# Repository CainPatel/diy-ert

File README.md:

# diy-ert

<!-- photo of the breadboard build / field setup goes here -->

A four electrode earth resistivity meter (Wenner array) built from scratch
in about a month, for roughly $150 in parts. Commercial instruments that
make the same measurement start above $20,000.

This repo is written as an engineering log. Four ADS1115 ADCs died during
development, all from the same root cause, and the
[failure log](docs/failure-log.md) is probably the most useful file here.
Read it before powering anything up.

The custom PCB, designed after the breadboard build below produced its
results. KiCad sources, gerbers, renders and review notes are in
[hardware/](hardware/README.md).

## Results

| Test | Result |
|---|---|
| Bench, known 100 Ω resistor | measured 98.6 Ω (1.4% error) |
| Field, moist Georgia clay, a = 0.5 m | 71-72 Ω·m apparent resistivity, 1.24 mA injected |

No 2D image yet. What exists today is a validated single point measurement
and one good field reading, both from the breadboard build. Full status
below.

## How it works

Contact resistance is the whole problem. Where a steel rod meets soil this
build measured 40-80 kΩ, and a two electrode measurement puts that
directly in series with the tens of ohms of ground you actually want. So
the roles are split across four electrodes: current goes in through the
outer pair (C1, C2), and the voltage it creates in the ground is read
across a separate inner pair (P1, P2). The potential pair feeds an
instrumentation amplifier and draws essentially no current, so its contact
resistance drops no voltage and falls out of the result. On the current
side, contact resistance only limits how much current flows, and the
current is measured across a shunt rather than assumed.

From there it is Ohm's law: R = V/I, and apparent resistivity
ρ = 2πa·R for electrode spacing a. Details in [docs/theory.md](docs/theory.md).

```mermaid
flowchart LR
    mega[Arduino]
    bridge[L298N H-bridge]
    muxa[MUX A]
    muxb[MUX B]
    muxcd[MUX C and D]
    amp[AD620]
    shunt["1 kΩ shunt"]
    adc[ADS1115]
    earth((earth))

    mega -->|IN1, IN2| bridge
    bridge --> muxa -->|C1| earth
    earth -->|C2| muxb --> shunt --> bridge
    earth -->|P1, P2| muxcd --> amp -->|A0| adc
    shunt -.->|A2, A3| adc
    adc -.->|I2C| mega
```

The H-bridge flips the injection polarity every ~150 ms. Differencing the
two half cycles cancels electrode self-potential and amplifier offset, and
stacking 20 cycles averages the noise down. The AD620 stage gain is 76 on
the breadboard build, measured with a multimeter during calibration rather
than taken from the trimmer setting. Four 16-channel muxes let any of 16
electrodes play any of the four roles.

## Status

- [x] Bench validation against a known resistor
- [x] One field reading
- [x] 16 channel electrode switching built on the breadboard, 12 of 16
      channels working (contact faults, see the failure log)
- [x] Automated Wenner survey firmware, outputs pyGIMLi format
- [x] Custom PCB designed: Arduino Nano plus shift registers, 2 layers,
      DRC clean, gerbers generated, firmware written and compiled
- [x] PCB fabricated, assembled and brought up (one design issue to settle
      first, see the review notes in [hardware/](hardware/README.md))
- [ ] Non-polarising potential electrodes (steel rods drift within minutes)
- [ ] 2D survey of real ground

## Documentation

In reading order:

1. [Theory](docs/theory.md): Ohm's law through the ground, Wenner
   geometry, why the polarity alternates, why stacking works
2. [Hardware](docs/hardware.md): the signal chain, wiring reference, and
   five design constraints learned the hard way
3. [Calibration](docs/calibration.md): the offset/gain procedure in the
   order that converges, with the numbers from this build
4. [Failure log](docs/failure-log.md): symptom, root cause, and fix for
   every failure, including the four dead ADCs
5. [Field procedure](docs/field-procedure.md): how the field reading was
   taken and what limits survey duration
6. [Build guide](docs/assembly.md): power, physical layout, every
   connection pin by pin, assembly order, pre-power checklist
7. [Software guide](docs/software.md): toolchain, uploading, the
   bring-up walkthrough, capturing a survey, running the inversion
8. [Firmware](firmware/README.md): seven bring-up sketches for the
   breadboard and one for the PCB. Run them in order.
9. [PCB](hardware/README.md): the board, what changed from the
   breadboard, shift register wiring, BOM, fabrication, review notes

## Repository layout

```
diy-ert/
├── docs/          theory, hardware, calibration, failure log, field
│                  procedure, build guide, software guide
├── firmware/      bring-up sketches 00-06 (Mega breadboard), 07 (Nano PCB)
├── hardware/      PCB: KiCad sources, gerbers, renders, schematic PDF,
│                  BOM, DRC/ERC reports
├── analysis/      pyGIMLi inversion script, capture cleaner, format notes
└── data/          data format spec and the one validated field reading
```

## Cost

Roughly $150 in parts including spares. The PCB bill of materials is in
[hardware/README.md](hardware/README.md); the parts that are not on the
board (rods, supply, wire, the breadboard-only trimmers) are listed in
the [build guide](docs/assembly.md).

## License

MIT, see [LICENSE](LICENSE).

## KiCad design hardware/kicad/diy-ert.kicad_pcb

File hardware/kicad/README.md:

# KiCad project

KiCad 10.0.5 sources for the diy-ert board.

| File | What |
|---|---|
| `diy-ert.kicad_pro` | project settings, design rules, net classes |
| `diy-ert.kicad_sch` | schematic, one A4 sheet |
| `diy-ert.kicad_pcb` | board, 2 layers, 127.05 x 117.55 mm |

Open `diy-ert.kicad_pro` in KiCad 10 or newer. Every symbol and footprint
comes from the standard KiCad libraries, so nothing else needs installing.
The `.kicad_prl` file (per-machine view settings) and the `.history/`
backup directory that KiCad creates are ignored by git.

The project was drawn under the default name `Untitled` and renamed here;
the rename touched only the project-name strings in the files, and the
netlist, ERC, DRC, and gerbers exported from the renamed project match the
originals.

## Regenerating the exports

Everything in the parent directory (schematic PDF, board renders, BOM,
reports, gerbers) is produced from these sources with `kicad-cli`:

```
kicad-cli sch export pdf -o ../schematic.pdf diy-ert.kicad_sch
kicad-cli sch export bom -o ../bom.csv --fields "Reference,Value,Footprint,\${QUANTITY}" --group-by "Value,Footprint" diy-ert.kicad_sch
kicad-cli sch erc -o ../reports/erc.rpt --severity-all diy-ert.kicad_sch
kicad-cli pcb drc -o ../reports/drc.rpt --severity-all diy-ert.kicad_pcb
kicad-cli pcb render -o ../images/pcb-top.png --side top --width 1500 --height 1400 diy-ert.kicad_pcb
kicad-cli pcb render -o ../images/pcb-bottom.png --side bottom --width 1500 --height 1400 diy-ert.kicad_pcb
kicad-cli pcb export gerbers -o ../gerbers/ --no-protel-ext --layers "F.Cu,B.Cu,F.SilkS,B.SilkS,F.Mask,B.Mask,Edge.Cuts" diy-ert.kicad_pcb
kicad-cli pcb export drill -o ../gerbers/ diy-ert.kicad_pcb
```

On macOS `kicad-cli` lives at
`/Applications/KiCad/KiCad.app/Contents/MacOS/kicad-cli`.

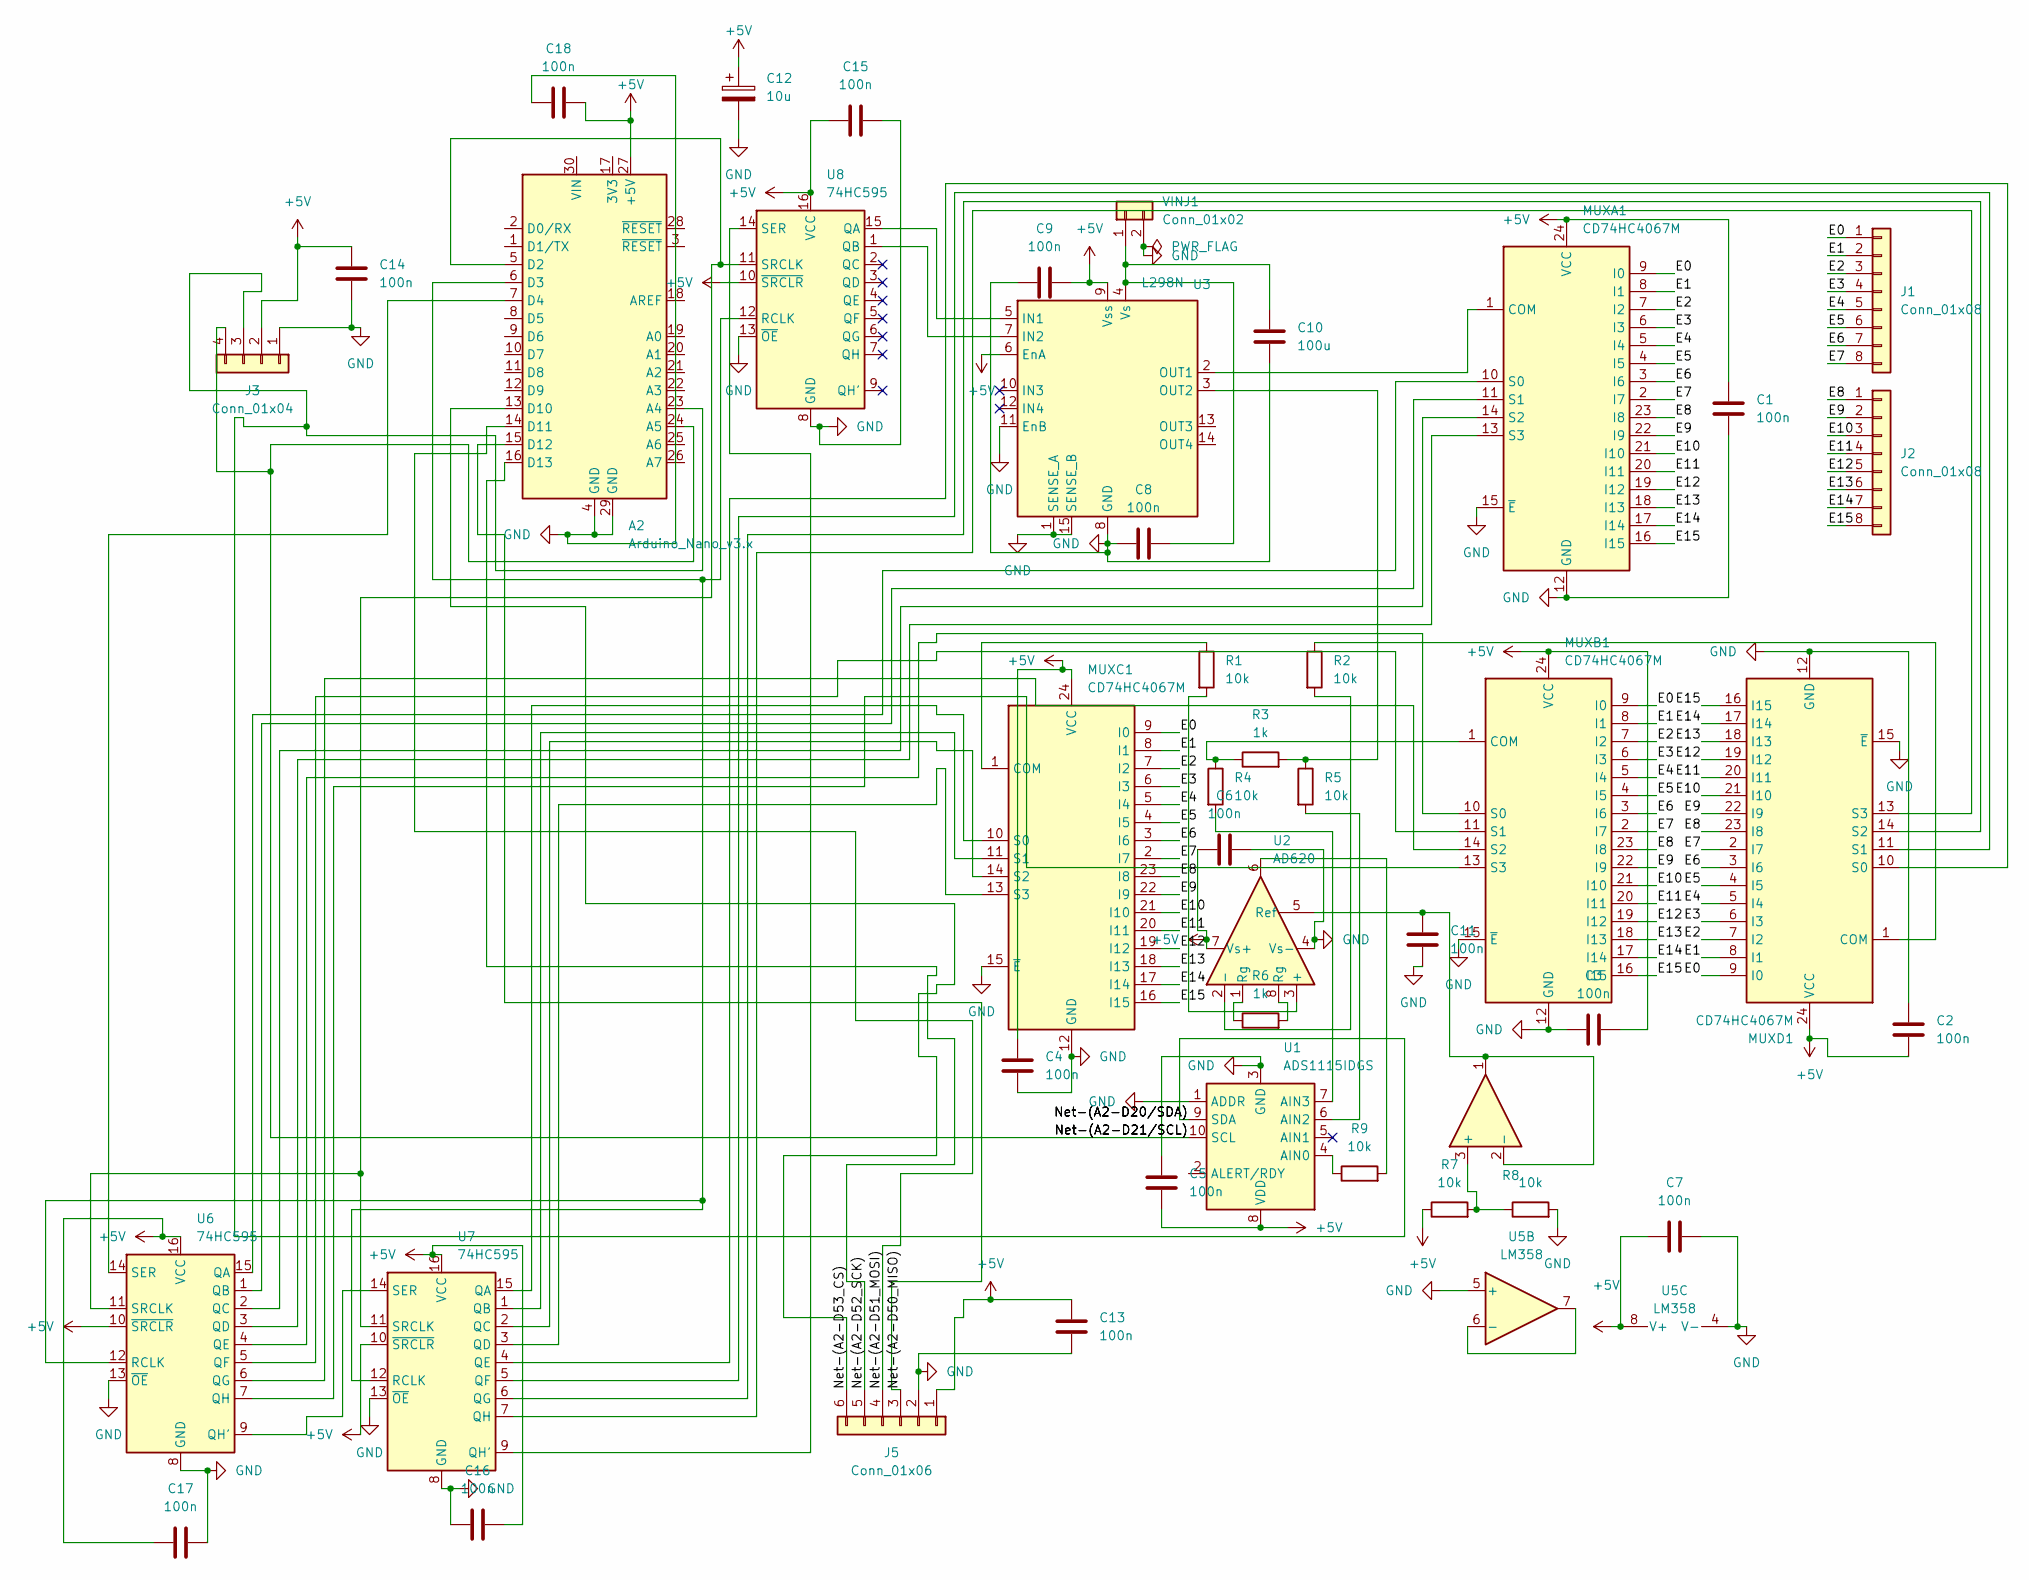
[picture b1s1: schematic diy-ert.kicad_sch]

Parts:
A2: Arduino_Nano_v3.x; Arduino_Nano
C1, C2, C3, C4, C5, C6, C7, C8, C9, C11, C13, C14, C15, C16, C17, C18: 100n; C_Disc_D5.0mm_W2.5mm_P5.00mm
C10: 100u; CP_Radial_D5.0mm_P2.50mm
C12: 10u; CP_Radial_D5.0mm_P2.50mm
J1, J2: Conn_01x08; TerminalBlock_Phoenix_MPT-0,5-8-2.54_1x08_P2.54mm_Horizontal
J3: Conn_01x04; PinSocket_1x04_P2.54mm_Vertical
J5: Conn_01x06; PinSocket_1x06_P2.54mm_Vertical
MUXA1: CD74HC4067M; DIP-24_W15.24mm
MUXB1: CD74HC4067M; DIP-24_W15.24mm
MUXC1: CD74HC4067M; DIP-24_W15.24mm
MUXD1: CD74HC4067M; DIP-24_W15.24mm
R1, R2, R4, R5, R7, R8, R9: 10k; R_Axial_DIN0207_L6.3mm_D2.5mm_P10.16mm_Horizontal
R3, R6: 1k; R_Axial_DIN0207_L6.3mm_D2.5mm_P10.16mm_Horizontal
U1: ADS1115IDGS; PinSocket_1x10_P2.54mm_Vertical
U2: AD620; DIP-8_W7.62mm
U3: L298N; TO-220-15_P2.54x5.08mm_StaggerOdd_Lead4.58mm_Vertical
U5: LM358; DIP-8_W7.62mm
U6, U7, U8: 74HC595; DIP-16_W7.62mm_Socket
VINJ1: Conn_01x02; TerminalBlock_Phoenix_MPT-0,5-2-2.54_1x02_P2.54mm_Horizontal

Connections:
+5V: A2.27 (+5V), C1.1, C2.2, C3.2, C4.2, C5.1, C6.2, C7.1, C9.2, C12.1, C13.1, C14.1, C15.1, C16.2, C17.2, C18.2, J3.2, J5.1, MUXA1.24 (VCC), MUXB1.24 (VCC), MUXC1.24 (VCC), MUXD1.24 (VCC), R7.1, U1.8 (VDD), U2.7 (Vs+), U3.6 (EnA), U3.9 (Vss), U5.8 (V+), U6.10 (~SRCLR), U6.16 (VCC), U7.10 (~SRCLR), U7.16 (VCC), U8.10 (~SRCLR), U8.16 (VCC)
/E0: J1.1, MUXA1.9 (I0), MUXB1.9 (I0), MUXC1.9 (I0), MUXD1.9 (I0)
/E1: J1.2, MUXA1.8 (I1), MUXB1.8 (I1), MUXC1.8 (I1), MUXD1.8 (I1)
/E2: J1.3, MUXA1.7 (I2), MUXB1.7 (I2), MUXC1.7 (I2), MUXD1.7 (I2)
/E3: J1.4, MUXA1.6 (I3), MUXB1.6 (I3), MUXC1.6 (I3), MUXD1.6 (I3)
/E4: J1.5, MUXA1.5 (I4), MUXB1.5 (I4), MUXC1.5 (I4), MUXD1.5 (I4)
/E5: J1.6, MUXA1.4 (I5), MUXB1.4 (I5), MUXC1.4 (I5), MUXD1.4 (I5)
/E6: J1.7, MUXA1.3 (I6), MUXB1.3 (I6), MUXC1.3 (I6), MUXD1.3 (I6)
/E7: J1.8, MUXA1.2 (I7), MUXB1.2 (I7), MUXC1.2 (I7), MUXD1.2 (I7)
/E8: J2.1, MUXA1.23 (I8), MUXB1.23 (I8), MUXC1.23 (I8), MUXD1.23 (I8)
/E9: J2.2, MUXA1.22 (I9), MUXB1.22 (I9), MUXC1.22 (I9), MUXD1.22 (I9)
/E10: J2.3, MUXA1.21 (I10), MUXB1.21 (I10), MUXC1.21 (I10), MUXD1.21 (I10)
/E11: J2.4, MUXA1.20 (I11), MUXB1.20 (I11), MUXC1.20 (I11), MUXD1.20 (I11)
/E12: J2.5, MUXA1.19 (I12), MUXB1.19 (I12), MUXC1.19 (I12), MUXD1.19 (I12)
/E13: J2.6, MUXA1.18 (I13), MUXB1.18 (I13), MUXC1.18 (I13), MUXD1.18 (I13)
/E14: J2.7, MUXA1.17 (I14), MUXB1.17 (I14), MUXC1.17 (I14), MUXD1.17 (I14)
/E15: J2.8, MUXA1.16 (I15), MUXB1.16 (I15), MUXC1.16 (I15), MUXD1.16 (I15)
/Net-(A2-D20/SDA): A2.23 (A4), J3.3, U1.9 (SDA)
/Net-(A2-D21/SCL): A2.24 (A5), J3.4, U1.10 (SCL)
/Net-(A2-D50_MISO): A2.15 (D12), J5.3
/Net-(A2-D51_MOSI): A2.14 (D11), J5.4
/Net-(A2-D52_SCK): A2.16 (D13), J5.5
/Net-(A2-D53_CS): A2.13 (D10), J5.6
GND: A2.4 (GND), A2.29 (GND), C1.2, C2.1, C3.1, C4.1, C5.2, C6.1, C7.2, C8.1, C9.1, C10.2, C11.2, C12.2, C13.2, C14.2, C15.2, C16.1, C17.1, C18.1, J3.1, J5.2, MUXA1.12 (GND), MUXA1.15 (~E), MUXB1.12 (GND), MUXB1.15 (~E), MUXC1.12 (GND), MUXC1.15 (~E), MUXD1.12 (GND), MUXD1.15 (~E), R8.2, U1.1 (ADDR), U1.3 (GND), U2.4 (Vs-), U3.1 (SENSE_A), U3.8 (GND), U3.11 (EnB), U3.15 (SENSE_B), U5.4 (V-), U5.5 (+), U6.8 (GND), U6.13 (~OE), U7.8 (GND), U7.13 (~OE), U8.8 (GND), U8.13 (~OE), VINJ1.2
unnamed: A2.5 (D2), U6.11 (SRCLK), U7.11 (SRCLK), U8.11 (SRCLK)
unnamed: A2.6 (D3), U6.12 (RCLK), U7.12 (RCLK), U8.12 (RCLK)
unnamed: A2.7 (D4), U6.14 (SER)
unnamed: MUXA1.1 (COM), U3.2 (OUT1)
unnamed: MUXA1.10 (S0), U6.15 (QA)
unnamed: MUXA1.11 (S1), U6.1 (QB)
unnamed: MUXA1.14 (S2), U6.2 (QC)
unnamed: MUXA1.13 (S3), U6.3 (QD)
unnamed: MUXB1.1 (COM), R3.1, R4.1
unnamed: MUXB1.10 (S0), U6.4 (QE)
unnamed: MUXB1.11 (S1), U6.5 (QF)
unnamed: MUXB1.14 (S2), U6.6 (QG)
unnamed: MUXB1.13 (S3), U6.7 (QH)
unnamed: MUXC1.1 (COM), R1.1
unnamed: MUXC1.10 (S0), U7.15 (QA)
unnamed: MUXC1.11 (S1), U7.1 (QB)
unnamed: MUXC1.14 (S2), U7.2 (QC)
unnamed: MUXC1.13 (S3), U7.3 (QD)
unnamed: MUXD1.1 (COM), R2.1
unnamed: MUXD1.10 (S0), U7.4 (QE)
unnamed: MUXD1.11 (S1), U7.5 (QF)
unnamed: MUXD1.14 (S2), U7.6 (QG)
unnamed: MUXD1.13 (S3), U7.7 (QH)
unnamed: R6.1, U2.1 (Rg)
unnamed: R6.2, U2.8 (Rg)
unnamed: R9.2, U2.6
unnamed: R9.1, U1.4 (AIN0)
unnamed: R5.2, U1.6 (AIN2)
unnamed: R4.2, U1.7 (AIN3)
unnamed: R1.2, U2.3 (+)
unnamed: R2.2, U2.2 (-)
unnamed: C11.1, U2.5 (Ref), U5.1, U5.2 (-)
unnamed: U3.5 (IN1), U8.15 (QA)
unnamed: U3.7 (IN2), U8.1 (QB)
unnamed: R3.2, R5.1, U3.3 (OUT2)
unnamed: C8.2, C10.1, U3.4 (Vs), VINJ1.1
unnamed: R7.2, R8.1, U5.3 (+)
unnamed: U5.6 (-), U5.7
unnamed: U6.9 (QH'), U7.14 (SER)
unnamed: U7.9 (QH'), U8.14 (SER)

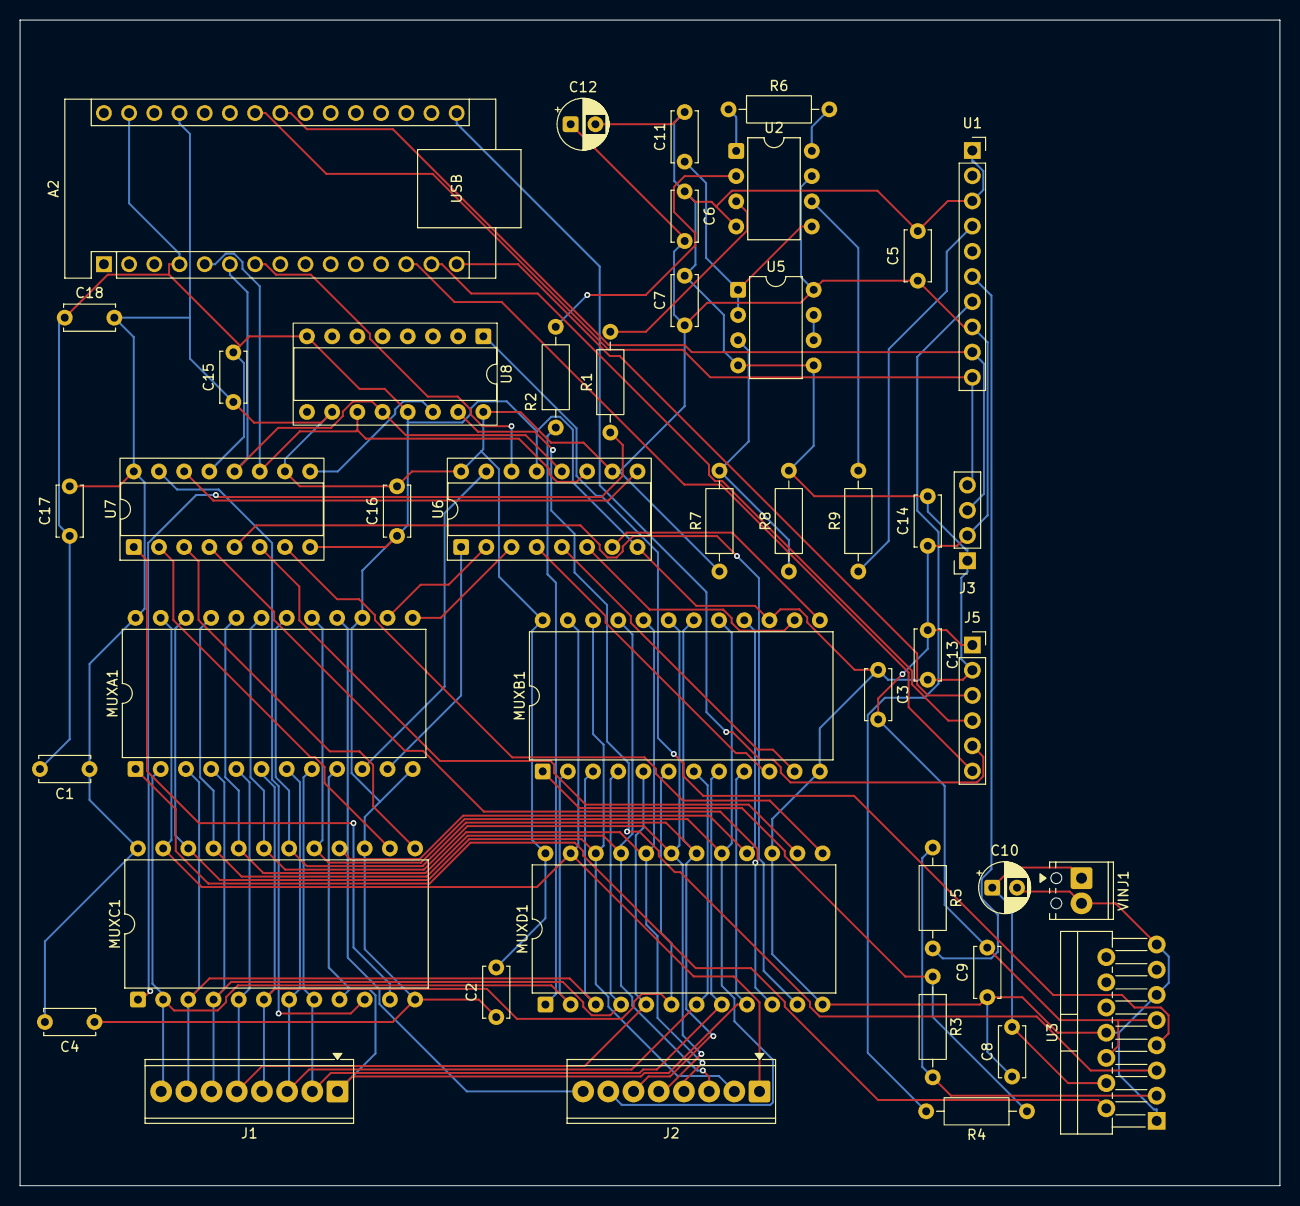
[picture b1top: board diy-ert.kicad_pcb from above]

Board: 2 copper layers, 127.0 x 117.5 mm, 44 parts (0 on the bottom side), 64 nets.

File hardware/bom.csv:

"Reference","Value","Footprint","QUANTITY"
"A2","Arduino_Nano_v3.x","Module:Arduino_Nano","1"
"C1-C9,C11,C13-C18","100n","Capacitor_THT:C_Disc_D5.0mm_W2.5mm_P5.00mm","16"
"C10","100u","Capacitor_THT:CP_Radial_D5.0mm_P2.50mm","1"
"C12","10u","Capacitor_THT:CP_Radial_D5.0mm_P2.50mm","1"
"J1,J2","Conn_01x08","TerminalBlock_Phoenix:TerminalBlock_Phoenix_MPT-0,5-8-2.54_1x08_P2.54mm_Horizontal","2"
"J3","Conn_01x04","Connector_PinSocket_2.54mm:PinSocket_1x04_P2.54mm_Vertical","1"
"J5","Conn_01x06","Connector_PinSocket_2.54mm:PinSocket_1x06_P2.54mm_Vertical","1"
"MUXA1,MUXB1,MUXC1,MUXD1","CD74HC4067M","Package_DIP:DIP-24_W15.24mm","4"
"R1,R2,R4,R5,R7-R9","10k","Resistor_THT:R_Axial_DIN0207_L6.3mm_D2.5mm_P10.16mm_Horizontal","7"
"R3,R6","1k","Resistor_THT:R_Axial_DIN0207_L6.3mm_D2.5mm_P10.16mm_Horizontal","2"
"U1","ADS1115IDGS","Connector_PinSocket_2.54mm:PinSocket_1x10_P2.54mm_Vertical","1"
"U2","AD620","Package_DIP:DIP-8_W7.62mm","1"
"U3","L298N","Package_TO_SOT_THT:TO-220-15_P2.54x5.08mm_StaggerOdd_Lead4.58mm_Vertical","1"
"U5","LM358","Package_DIP:DIP-8_W7.62mm","1"
"U6-U8","74HC595","Package_DIP:DIP-16_W7.62mm_Socket","3"
"VINJ1","Conn_01x02","TerminalBlock_Phoenix:TerminalBlock_Phoenix_MPT-0,5-2-2.54_1x02_P2.54mm_Horizontal","1"
